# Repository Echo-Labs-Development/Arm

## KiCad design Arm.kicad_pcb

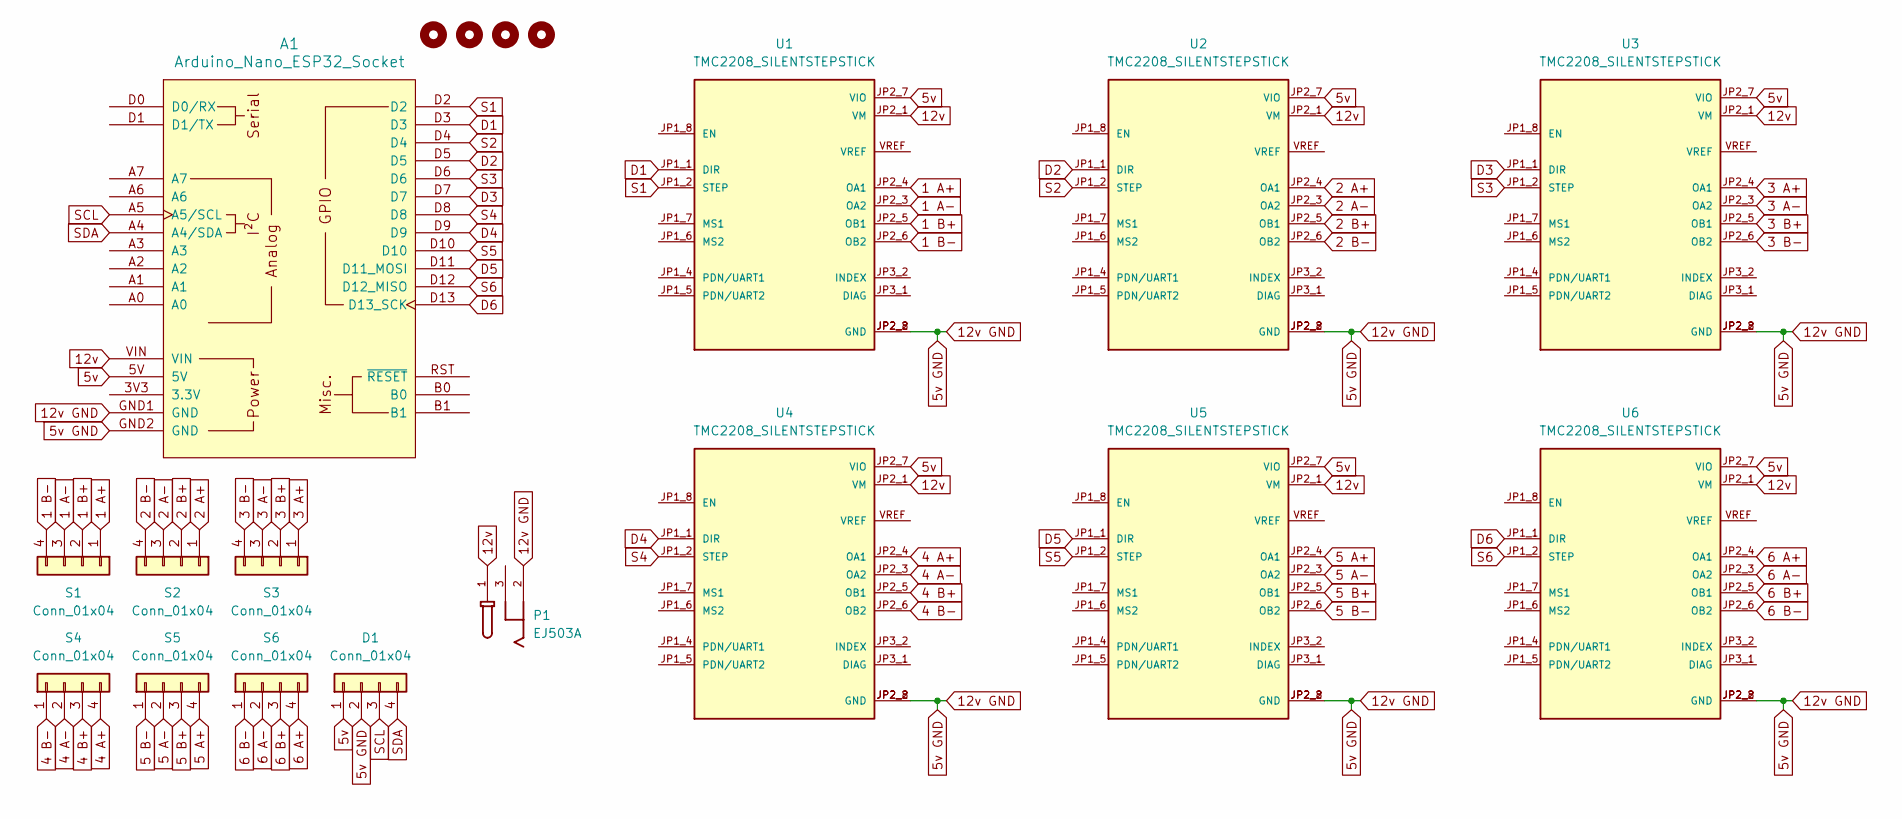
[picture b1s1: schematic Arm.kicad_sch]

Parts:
A1: Arduino_Nano_ESP32_Socket
D1: Conn_01x04; JST_EH_B4B-EH-A_1x04_P2.50mm_Vertical
H1, H2, H3, H4: MountingHole; MountingHole_3.2mm_M3
P1: EJ503A; MPD_EJ503A; PARTREV B
S1, S2, S3, S4, S5, S6: Conn_01x04; JST_EH_B4B-EH-A_1x04_P2.50mm_Vertical
U1, U2, U3, U4, U5, U6: TMC2208_SILENTSTEPSTICK; MODULE_TMC2208_SILENTSTEPSTICK

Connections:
1 A+: S1.1, U1.JP2_4 (OA1)
1 A-: S1.3, U1.JP2_3 (OA2)
1 B+: S1.2, U1.JP2_5 (OB1)
1 B-: S1.4, U1.JP2_6 (OB2)
2 A+: S2.1, U2.JP2_4 (OA1)
2 A-: S2.3, U2.JP2_3 (OA2)
2 B+: S2.2, U2.JP2_5 (OB1)
2 B-: S2.4, U2.JP2_6 (OB2)
3 A+: S3.1, U3.JP2_4 (OA1)
3 A-: S3.3, U3.JP2_3 (OA2)
3 B+: S3.2, U3.JP2_5 (OB1)
3 B-: S3.4, U3.JP2_6 (OB2)
4 A+: S4.4, U4.JP2_4 (OA1)
4 A-: S4.2, U4.JP2_3 (OA2)
4 B+: S4.3, U4.JP2_5 (OB1)
4 B-: S4.1, U4.JP2_6 (OB2)
5 A+: S5.4, U5.JP2_4 (OA1)
5 A-: S5.2, U5.JP2_3 (OA2)
5 B+: S5.3, U5.JP2_5 (OB1)
5 B-: S5.1, U5.JP2_6 (OB2)
5v: A1.5V, D1.1, U1.JP2_7 (VIO), U2.JP2_7 (VIO), U3.JP2_7 (VIO), U4.JP2_7 (VIO), U5.JP2_7 (VIO), U6.JP2_7 (VIO)
6 A+: S6.4, U6.JP2_4 (OA1)
6 A-: S6.2, U6.JP2_3 (OA2)
6 B+: S6.3, U6.JP2_5 (OB1)
6 B-: S6.1, U6.JP2_6 (OB2)
12v: A1.VIN, P1.1, U1.JP2_1 (VM), U2.JP2_1 (VM), U3.JP2_1 (VM), U4.JP2_1 (VM), U5.JP2_1 (VM), U6.JP2_1 (VM)
12v GND: A1.GND1 (GND), A1.GND2 (GND), D1.2, P1.2, U1.JP2_2 (GND), U1.JP2_8 (GND), U2.JP2_2 (GND), U2.JP2_8 (GND), U3.JP2_2 (GND), U3.JP2_8 (GND), U4.JP2_2 (GND), U4.JP2_8 (GND), U5.JP2_2 (GND), U5.JP2_8 (GND), U6.JP2_2 (GND), U6.JP2_8 (GND)
D1: A1.D3, U1.JP1_1 (DIR)
D2: A1.D5, U2.JP1_1 (DIR)
D3: A1.D7, U3.JP1_1 (DIR)
D4: A1.D9, U4.JP1_1 (DIR)
D5: A1.D11 (D11_MOSI), U5.JP1_1 (DIR)
D6: A1.D13 (D13_SCK), U6.JP1_1 (DIR)
S1: A1.D2, U1.JP1_2 (STEP)
S2: A1.D4, U2.JP1_2 (STEP)
S3: A1.D6, U3.JP1_2 (STEP)
S4: A1.D8, U4.JP1_2 (STEP)
S5: A1.D10, U5.JP1_2 (STEP)
S6: A1.D12 (D12_MISO), U6.JP1_2 (STEP)
SCL: A1.A5 (A5/SCL), D1.3
SDA: A1.A4 (A4/SDA), D1.4

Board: 2 copper layers, 19 parts (0 on the bottom side), 41 nets, no tracks yet.

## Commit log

2024-08-24 Add Schematic
2024-08-24 Update Schematic and Start PCB
